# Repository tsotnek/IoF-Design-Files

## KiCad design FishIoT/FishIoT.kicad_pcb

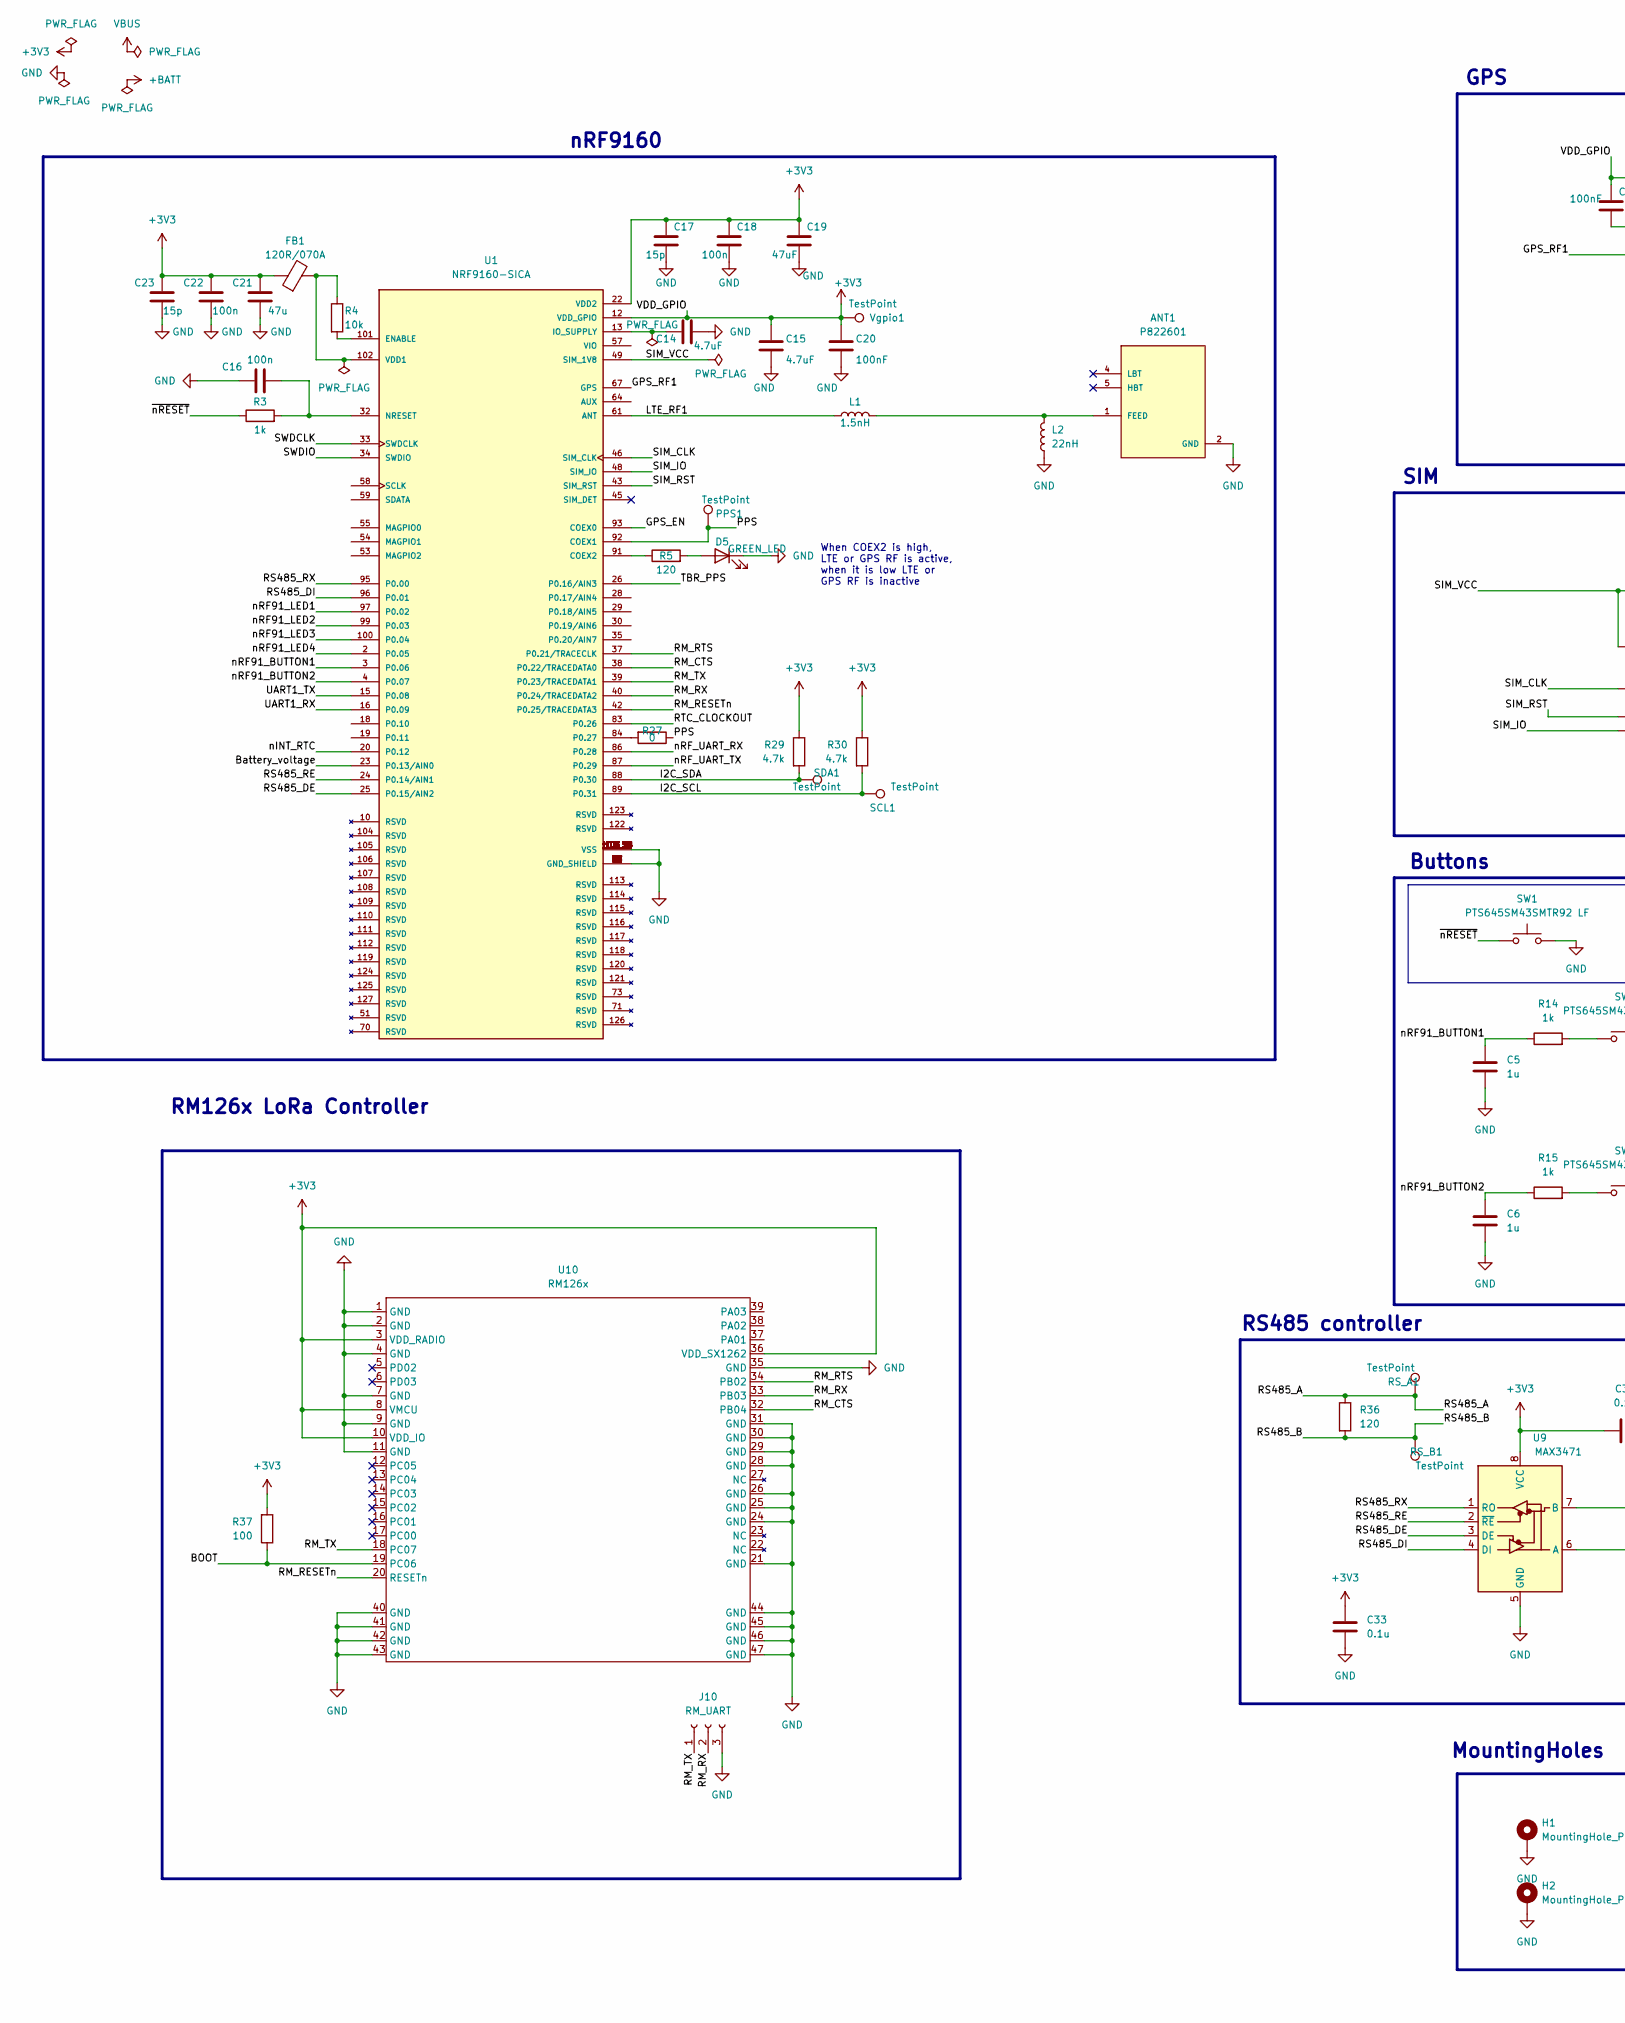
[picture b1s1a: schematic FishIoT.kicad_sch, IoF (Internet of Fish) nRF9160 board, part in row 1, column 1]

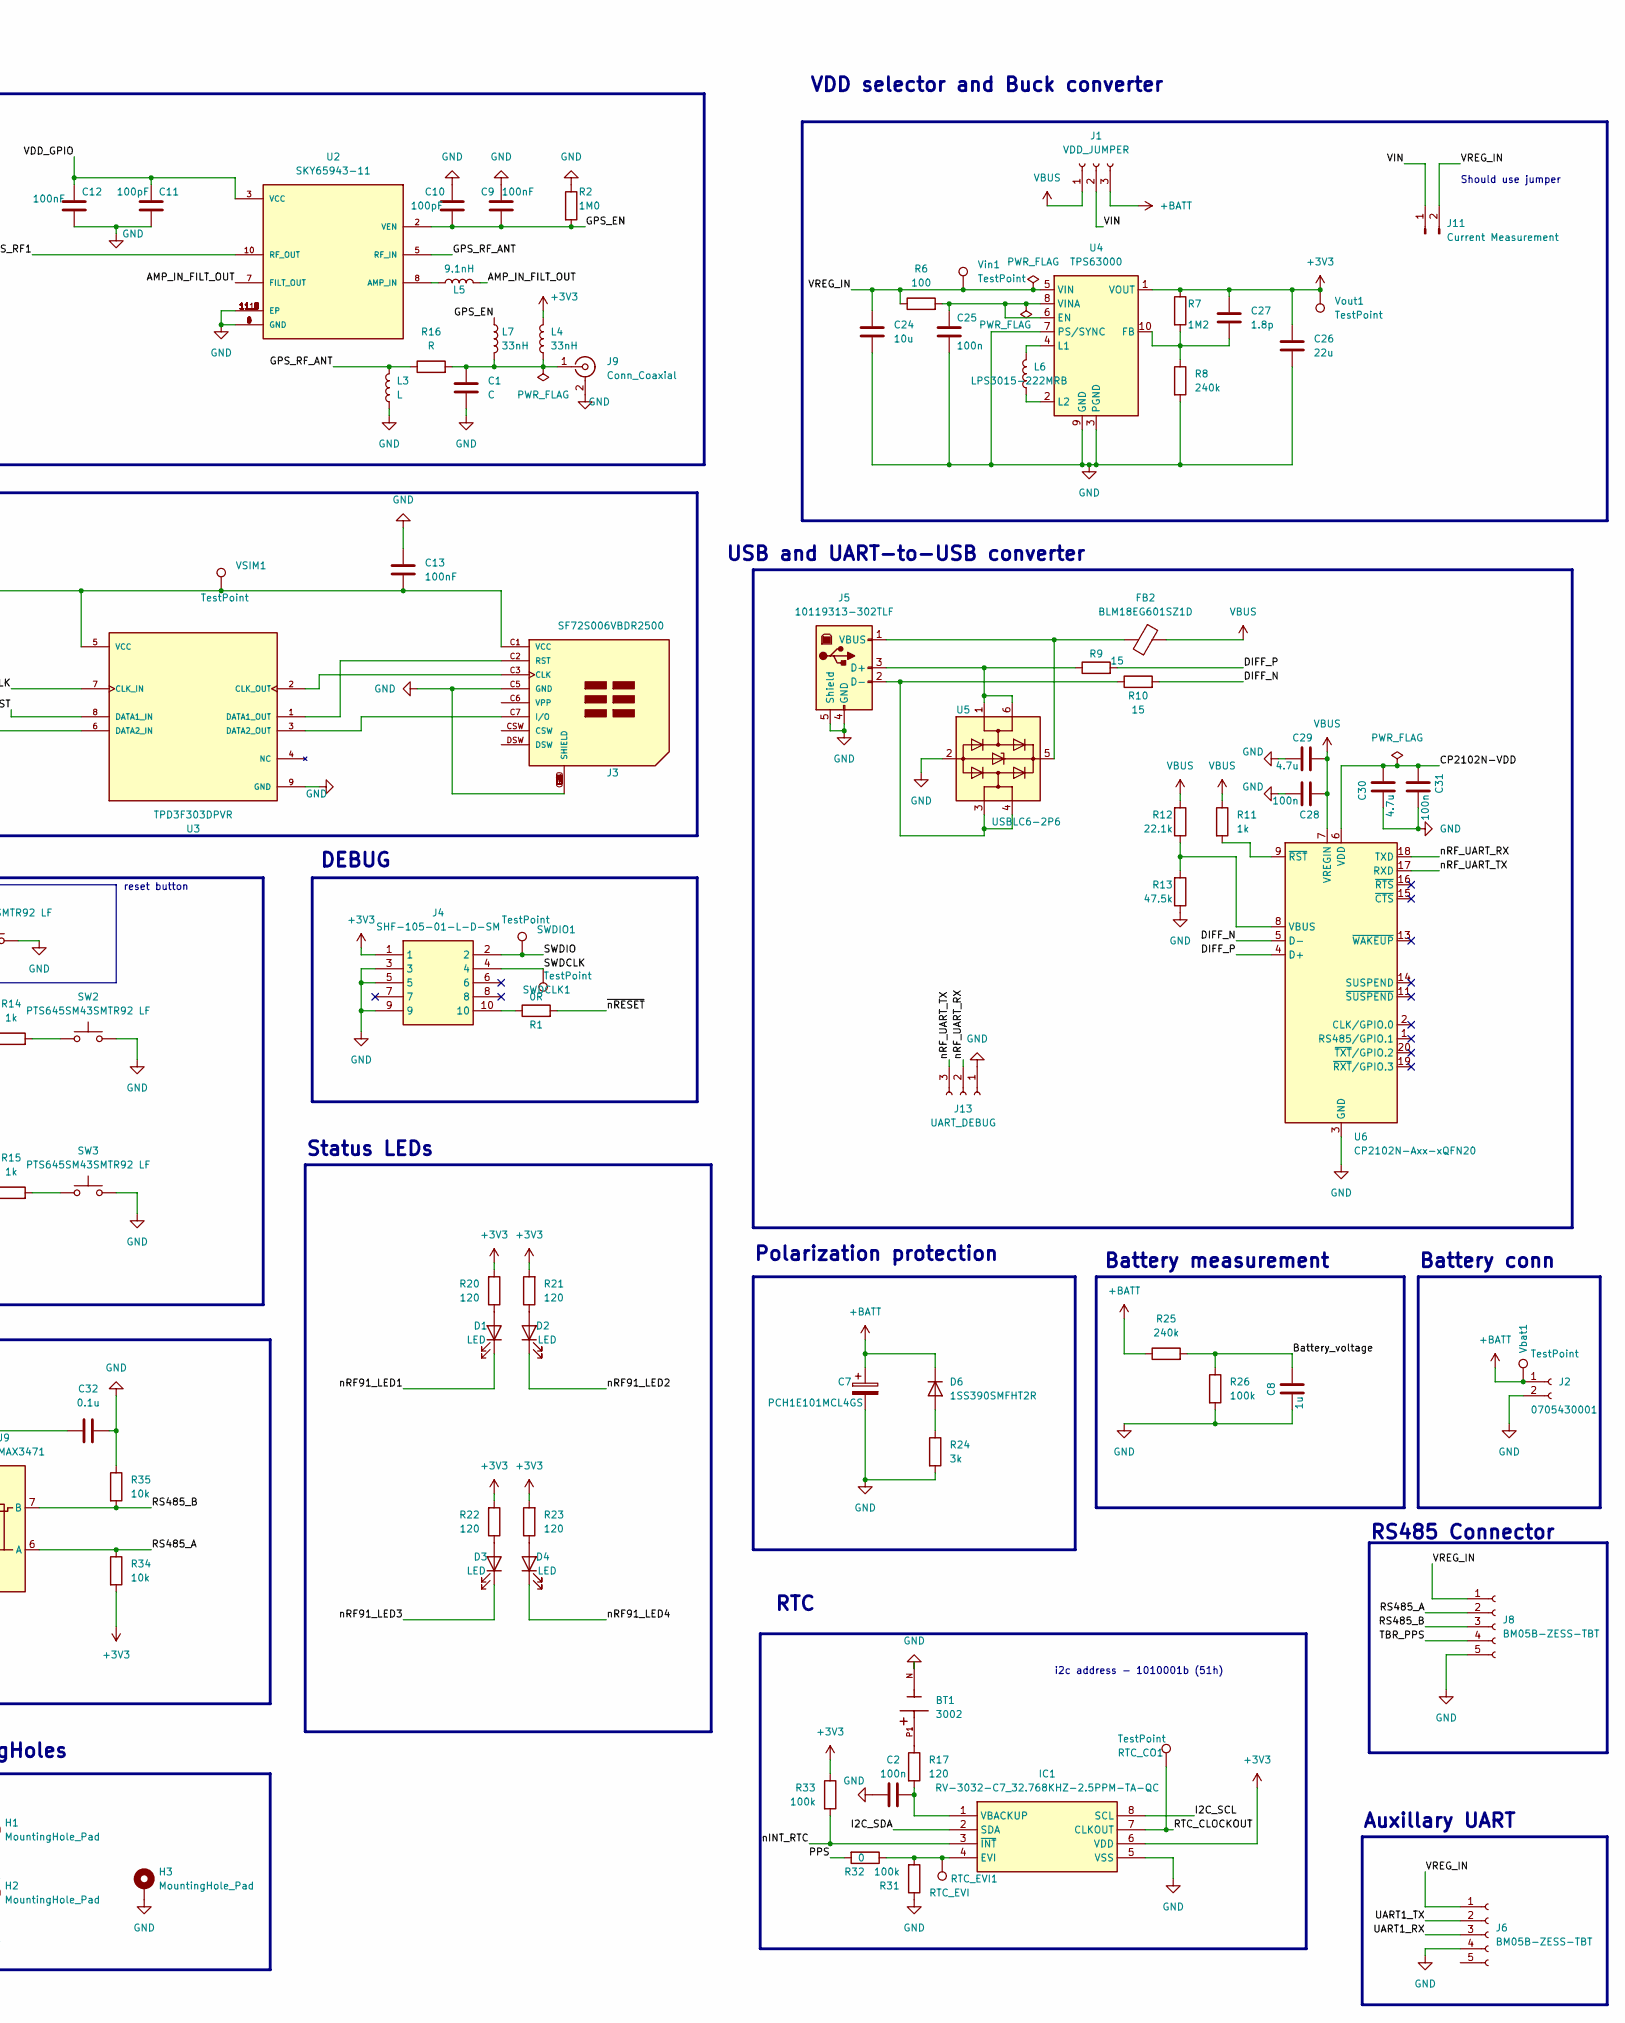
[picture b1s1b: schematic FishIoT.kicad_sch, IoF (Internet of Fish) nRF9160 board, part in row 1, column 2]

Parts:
ANT1: P822601; ANT_P822601
BT1: 3002; BAT_3002; PARTREV A
C1: C; C_0603_1608Metric
C2, C16, C18, C22, C25, C28, C31: 100n; C_0603_1608Metric
C5, C6, C8: 1u; C_0603_1608Metric
C7: PCH1E101MCL4GS; CP_Elec_6.3x7.7
C9, C12, C13, C20: 100nF; C_0603_1608Metric
C10, C11: 100pF; C_0603_1608Metric
C14, C15: 4.7uF; C_0603_1608Metric
C17, C23: 15p; C_0603_1608Metric
C19: 47uF; C_0603_1608Metric
C21: 47u; C_0603_1608Metric
C24: 10u; C_0603_1608Metric
C26: 22u; C_0603_1608Metric
C27: 1.8p; C_0603_1608Metric
C29, C30: 4.7u; C_0603_1608Metric
C32, C33: 0.1u; C_0603_1608Metric
D1, D2, D3, D4: LED; LED_0603_1608Metric
D5: GREEN_LED; LED_0603_1608Metric
D6: 1SS390SMFHT2R; D_SOD-523
FB1: 120R/070A; L_0603_1608Metric
FB2: BLM18EG601SZ1D; L_0603_1608Metric
H1, H2, H3: MountingHole_Pad; MountingHole_3mm_Pad_Via
IC1: RV-3032-C7_32.768KHZ-2.5PPM-TA-QC; RV3032C7; Mouser Part Number 428-203803-MG01
J1: VDD_JUMPER; PinHeader_1x03_P2.54mm_Vertical
J2: 0705430001; MOLEX_0705430001
J3: SF72S006VBDR2500; JAE_SF72S006VBDR2500
J4: SHF-105-01-L-D-SM; SHF-105-01-X-D-SM; Mouser Part Number 200-SHF10501LDSM
J5: 10119313-302TLF; AMPHENOL_10119313-302TLF
J6, J8: BM05B-ZESS-TBT; BM05BZESSTBTLFSN
J9: Conn_Coaxial; LINX_CONUFL001-SMD-T
J10: RM_UART; PinHeader_1x03_P2.54mm_Vertical
J11: Current Measurement; PinHeader_1x02_P2.54mm_Vertical
J13: UART_DEBUG; PinHeader_1x03_P2.54mm_Vertical
L1: 1.5nH; L_0603_1608Metric
L2: 22nH; L_0603_1608Metric
L3: L; L_0603_1608Metric
L4, L7: 33nH; L_0603_1608Metric
L5: 9.1nH; L_0603_1608Metric
L6: LPS3015-222MRB; L_Vishay_IHLP-1212
PPS1: TestPoint; TestPoint_Pad_D1.0mm
R1: 0R; R_0603_1608Metric
R2: 1M0; R_0603_1608Metric
R3, R11, R14, R15: 1k; R_0603_1608Metric
R4, R34, R35: 10k; R_0603_1608Metric
R5, R17, R20, R21, R22, R23, R36: 120; R_0603_1608Metric
R6, R37: 100; R_0603_1608Metric
R7: 1M2; R_0603_1608Metric
R8, R25: 240k; R_0603_1608Metric
R9, R10: 15; R_0603_1608Metric
R12: 22.1k; R_0603_1608Metric
R13: 47.5k; R_0603_1608Metric
R16: R; R_0603_1608Metric
R24: 3k; R_0603_1608Metric
R26, R31, R33: 100k; R_0603_1608Metric
R27, R32: 0; R_0603_1608Metric
R29, R30: 4.7k; R_0603_1608Metric
RS_A1: TestPoint; TestPoint_Pad_D1.0mm
RS_B1: TestPoint; TestPoint_Pad_D1.0mm
RTC_CO1: TestPoint; TestPoint_Pad_D1.0mm
RTC_EVI1: RTC_EVI; TestPoint_Pad_D1.0mm
SCL1: TestPoint; TestPoint_Pad_D1.0mm
SDA1: TestPoint; TestPoint_Pad_D1.0mm
SW1, SW2, SW3: PTS645SM43SMTR92 LF; SW_Push_1P1T_NO_6x6mm_H9.5mm
SWDCLK1: TestPoint; TestPoint_Pad_D1.0mm
SWDIO1: TestPoint; TestPoint_Pad_D1.0mm
U1: NRF9160-SICA; XCVR_NRF9160-SICA; PARTREV 0.7.1
U2: SKY65943-11; IC_SKY65943-11; PARTREV September 12, 2019
U3: TPD3F303DPVR; SON50P210X160X65-9N
U4: TPS63000; Texas_DRC0010J_ThermalVias
U5: USBLC6-2P6; SOT-666
U6: CP2102N-Axx-xQFN20; SiliconLabs_QFN-20-1EP_3x3mm_P0.5mm_EP1.8x1.8mm
U9: MAX3471; TSSOP-8_3x3mm_P0.65mm
U10: RM126x; Laird, RM126X
VSIM1: TestPoint; TestPoint_Pad_D1.0mm
Vbat1: TestPoint; TestPoint_Pad_D1.0mm
Vgpio1: TestPoint; TestPoint_Pad_D1.0mm
Vin1: TestPoint; TestPoint_Pad_D1.0mm
Vout1: TestPoint; TestPoint_Pad_D1.0mm

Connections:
+3V3: C11.2, C12.1, C15.1, C17.1, C18.1, C19.1, C20.1, C21.2, C22.2, C23.2, C26.1, C27.1, C32.2, C33.1, FB1.1, IC1.6 (VDD), J4.1, L4.2, R7.1, R20.2, R21.2, R22.2, R23.2, R29.1, R30.1, R33.1, R34.2, R37.2, U1.12 (VDD_GPIO), U1.22 (VDD2), U2.3 (VCC), U4.1 (VOUT), U9.8 (VCC), U10.3 (VDD_RADIO), U10.8 (VMCU), U10.10 (VDD_IO), U10.36 (VDD_SX1262), Vgpio1.1, Vout1.1
+BATT: C7.1, D6.1 (K), J1.3, J2.1, R25.1, Vbat1.1
/AMP_IN_FILT_OUT: L5.2, U2.7 (FILT_OUT)
/BOOT: R37.1, U10.19 (PC06)
/Battery_voltage: C8.2, R25.2, R26.1, U1.23 (P0.13/AIN0)
/CP2102N-VDD: C30.2, C31.2, U6.6 (VDD)
/DIFF_N: R10.2, U6.5 (D-)
/DIFF_P: R9.2, U6.4 (D+)
/GPS_EN: C9.1, C10.2, L7.1, R2.2, U1.93 (COEX0), U2.2 (VEN)
/GPS_RF1: U1.67 (GPS), U2.10 (RF_OUT)
/GPS_RF_ANT: L3.2, R16.1, U2.5 (RF_IN)
/I2C_SCL: IC1.8 (SCL), R30.2, SCL1.1, U1.89 (P0.31)
/I2C_SDA: IC1.2 (SDA), R29.2, SDA1.1, U1.88 (P0.30)
/LTE_RF1: L1.1, U1.61 (ANT)
/PPS: PPS1.1, R27.1, R32.2, U1.92 (COEX1)
/RM_CTS: U1.38 (P0.22/TRACEDATA0), U10.32 (PB04)
/RM_RESETn: U1.42 (P0.25/TRACEDATA3), U10.20 (RESETn)
/RM_RTS: U1.37 (P0.21/TRACECLK), U10.34 (PB02)
/RM_RX: J10.2, U1.40 (P0.24/TRACEDATA2), U10.33 (PB03)
/RM_TX: J10.1, U1.39 (P0.23/TRACEDATA1), U10.18 (PC07)
/RS485_A: J8.2, R34.1, R36.1, RS_A1.1, U9.6 (A)
/RS485_B: J8.3, R35.2, R36.2, RS_B1.1, U9.7 (B)
/RS485_DE: U1.25 (P0.15/AIN2), U9.3 (DE)
/RS485_DI: U1.96 (P0.01), U9.4 (DI)
/RS485_RE: U1.24 (P0.14/AIN1), U9.2 (~RE)
/RS485_RX: U1.95 (P0.00), U9.1 (RO)
/RTC_CLOCKOUT: IC1.7 (CLKOUT), RTC_CO1.1, U1.83 (P0.26)
/SIM_CLK: U1.46 (SIM_CLK), U3.7 (CLK_IN)
/SIM_IO: U1.48 (SIM_IO), U3.6 (DATA2_IN)
/SIM_RST: U1.43 (SIM_RST), U3.8 (DATA1_IN)
/SIM_VCC: C13.2, J3.C1 (VCC), U1.49 (SIM_1V8), U3.5 (VCC), VSIM1.1
/SWDCLK: J4.4, SWDCLK1.1, U1.33 (SWDCLK)
/SWDIO: J4.2, SWDIO1.1, U1.34 (SWDIO)
/TBR_PPS: J8.4, U1.26 (P0.16/AIN3)
/UART1_RX: J6.3, U1.16 (P0.09)
/UART1_TX: J6.2, U1.15 (P0.08)
/VIN: J1.2, J11.1
/VREG_IN: C24.1, J6.1, J8.1, J11.2, R6.1, U4.5 (VIN), Vin1.1
/nINT_RTC: IC1.3 (~INT), R33.2, U1.20 (P0.12)
/nRF91_BUTTON1: C5.1, R14.1, U1.3 (P0.06)
/nRF91_BUTTON2: C6.1, R15.1, U1.4 (P0.07)
/nRF91_LED1: D1.1 (K), U1.97 (P0.02)
/nRF91_LED2: D2.1 (K), U1.99 (P0.03)
/nRF91_LED3: D3.1 (K), U1.100 (P0.04)
/nRF91_LED4: D4.1 (K), U1.2 (P0.05)
/nRF_UART_RX: J13.2, U1.86 (P0.28), U6.18 (TXD)
/nRF_UART_TX: J13.3, U1.87 (P0.29), U6.17 (RXD)
/~nRESET: R1.2, R3.1, SW1.1
GND: ANT1.2 (GND), BT1.N, C1.2, C2.1, C5.2, C6.2, C7.2, C8.1, C9.2, C10.1, C11.1, C12.2, C13.1, C14.1, C15.2, C16.1, C17.2, C18.2, C19.2, C20.2, C21.1, C22.1, C23.1, C24.2, C25.2, C26.2, C28.1, C29.1, C30.1, C31.1, C32.1, C33.2, D5.1 (K), H1.1, H2.1, H3.1, IC1.5 (VSS), J2.2, J3.C5 (GND), J3.G1 (SHIELD), J3.G2 (SHIELD), J3.G3 (SHIELD), J3.G4 (SHIELD), J3.G5 (SHIELD), J3.G6 (SHIELD), J3.G7 (SHIELD), J3.G8 (SHIELD), J3.G9 (SHIELD), J3.G10 (SHIELD), J4.3, J4.5, J4.9, J5.4 (GND), J5.5 (Shield), J6.4, J8.5, J9.2 (Ext), J10.3, J13.1, L2.1, L3.1, R2.1, R8.2, R13.1, R24.2, R26.2, R31.1, R35.1, SW1.2, SW2.2, SW3.2, U1.1 (GND_SHIELD), U1.5 (GND_SHIELD), U1.6 (GND_SHIELD), U1.7 (GND_SHIELD), U1.8 (GND_SHIELD), U1.9 (GND_SHIELD), U1.11 (GND_SHIELD), U1.14 (GND_SHIELD), U1.17 (GND_SHIELD), U1.21 (GND_SHIELD), U1.27 (GND_SHIELD), U1.31 (GND_SHIELD), U1.36 (GND_SHIELD), U1.41 (GND_SHIELD), U1.44 (GND_SHIELD), U1.47 (GND_SHIELD), U1.50 (GND_SHIELD), U1.52 (GND_SHIELD), U1.56 (GND_SHIELD), U1.60 (GND_SHIELD), U1.62 (GND_SHIELD), U1.63 (GND_SHIELD), U1.65 (GND_SHIELD), U1.66 (GND_SHIELD), U1.68 (GND_SHIELD), U1.69 (GND_SHIELD), U1.72 (GND_SHIELD), U1.74 (GND_SHIELD), U1.75 (GND_SHIELD), U1.76 (GND_SHIELD), U1.77 (GND_SHIELD), U1.78 (GND_SHIELD), U1.79 (GND_SHIELD), U1.80 (GND_SHIELD), U1.81 (GND_SHIELD), U1.82 (GND_SHIELD), U1.85 (GND_SHIELD), U1.90 (GND_SHIELD), U1.94 (GND_SHIELD), U1.98 (GND_SHIELD), U1.103_1 (VSS), U1.103_2 (VSS), U1.103_3 (VSS), U1.103_4 (VSS), U1.103_5 (VSS), U1.103_6 (VSS), U1.103_7 (VSS), U1.103_8 (VSS), U1.103_9 (VSS), U1.103_10 (VSS), U1.103_11 (VSS), U1.103_12 (VSS), U1.103_13 (VSS), U1.103_14 (VSS), U1.103_15 (VSS), U1.103_16 (VSS), U1.103_17 (VSS), U1.103_18 (VSS), U1.103_19 (VSS), U1.103_20 (VSS), U1.103_21 (VSS), U1.103_22 (VSS), U1.103_23 (VSS), U1.103_24 (VSS), U1.103_25 (VSS), U1.103_26 (VSS), U1.103_27 (VSS), U1.103_28 (VSS), U1.103_29 (VSS), U1.103_30 (VSS), U1.103_31 (VSS), U1.103_32 (VSS), U1.103_33 (VSS), U1.103_34 (VSS), U1.103_35 (VSS), U2.1 (GND), U2.4 (GND), U2.6 (GND), U2.9 (GND), U2.11 (EP), U2.11_1 (EP), U2.11_2 (EP), U2.11_3 (EP), U2.11_4 (EP), U2.11_5 (EP), U2.11_6 (EP), U2.11_7 (EP), U2.11_8 (EP), U3.9 (GND), U4.3 (PGND), U4.7 (PS/SYNC), U4.9 (GND), U4.11 (PGND), U5.2 (GND), U6.3 (GND), U6.12 (GND), U6.21 (GND), U9.5 (GND), U10.1 (GND), U10.2 (GND), U10.4 (GND), U10.7 (GND), U10.9 (GND), U10.11 (GND), U10.21 (GND), U10.24 (GND), U10.25 (GND), U10.26 (GND), U10.28 (GND), U10.29 (GND), U10.30 (GND), U10.31 (GND), U10.35 (GND), U10.40 (GND), U10.41 (GND), U10.42 (GND), U10.43 (GND), U10.44 (GND), U10.45 (GND), U10.46 (GND), U10.47 (GND)
unnamed: ANT1.1 (FEED), L1.2, L2.2
unnamed: BT1.P1, R17.1
unnamed: D1.2 (A), R20.1
unnamed: D2.2 (A), R21.1
unnamed: D3.2 (A), R22.1
unnamed: D4.2 (A), R23.1
unnamed: D5.2 (A), R5.2
unnamed: D6.2 (A), R24.1
unnamed: IC1.4 (EVI), R31.2, R32.1, RTC_EVI1.1
unnamed: C2.2, IC1.1 (VBACKUP), R17.2
unnamed: J3.C3 (CLK), U3.2 (CLK_OUT)
unnamed: J3.C7 (I/O), U3.3 (DATA2_OUT)
unnamed: J3.C2 (RST), U3.1 (DATA1_OUT)
unnamed: J4.10, R1.1
unnamed: J5.3 (D+), R9.1, U5.1 (I/O1), U5.6 (I/O1)
unnamed: J5.2 (D-), R10.1, U5.3 (I/O2), U5.4 (I/O2)
unnamed: FB2.2, J5.1 (VBUS), U5.5 (VBUS)
unnamed: C1.1, J9.1 (In), L4.1, L7.2, R16.2
unnamed: R14.2, SW2.1
unnamed: R15.2, SW3.1
unnamed: R5.1, U1.91 (COEX2)
unnamed: R4.2, U1.101 (ENABLE)
unnamed: C14.2, U1.13 (IO_SUPPLY)
unnamed: C16.2, R3.2, U1.32 (NRESET)
unnamed: R27.2, U1.84 (P0.27)
unnamed: FB1.2, R4.1, U1.102 (VDD1)
unnamed: L5.1, U2.8 (AMP_IN)
unnamed: C25.1, R6.2, U4.6 (EN), U4.8 (VINA)
unnamed: C27.2, R7.2, R8.1, U4.10 (FB)
unnamed: L6.2, U4.4 (L1)
unnamed: L6.1, U4.2 (L2)
unnamed: R12.1, R13.2, U6.8 (VBUS)
unnamed: R11.2, U6.9 (~RST)
VBUS: C28.2, C29.2, FB2.1, J1.1, R11.1, R12.2, U6.7 (VREGIN)

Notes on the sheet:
MountingHoles
Polarization protection
When COEX2 is high, LTE or GPS RF is active, when it is low LTE or GPS RF is inactive
Battery conn
Status LEDs
Auxillary UART
RTC
nRF9160
i2c address - 1010001b (51h)
USB and UART-to-USB converter
Buttons
VDD selector and Buck converter
GPS
RS485 Connector
DEBUG
reset button
RS485 controller
SIM
Should use jumper
RM126x LoRa Controller
Battery measurement

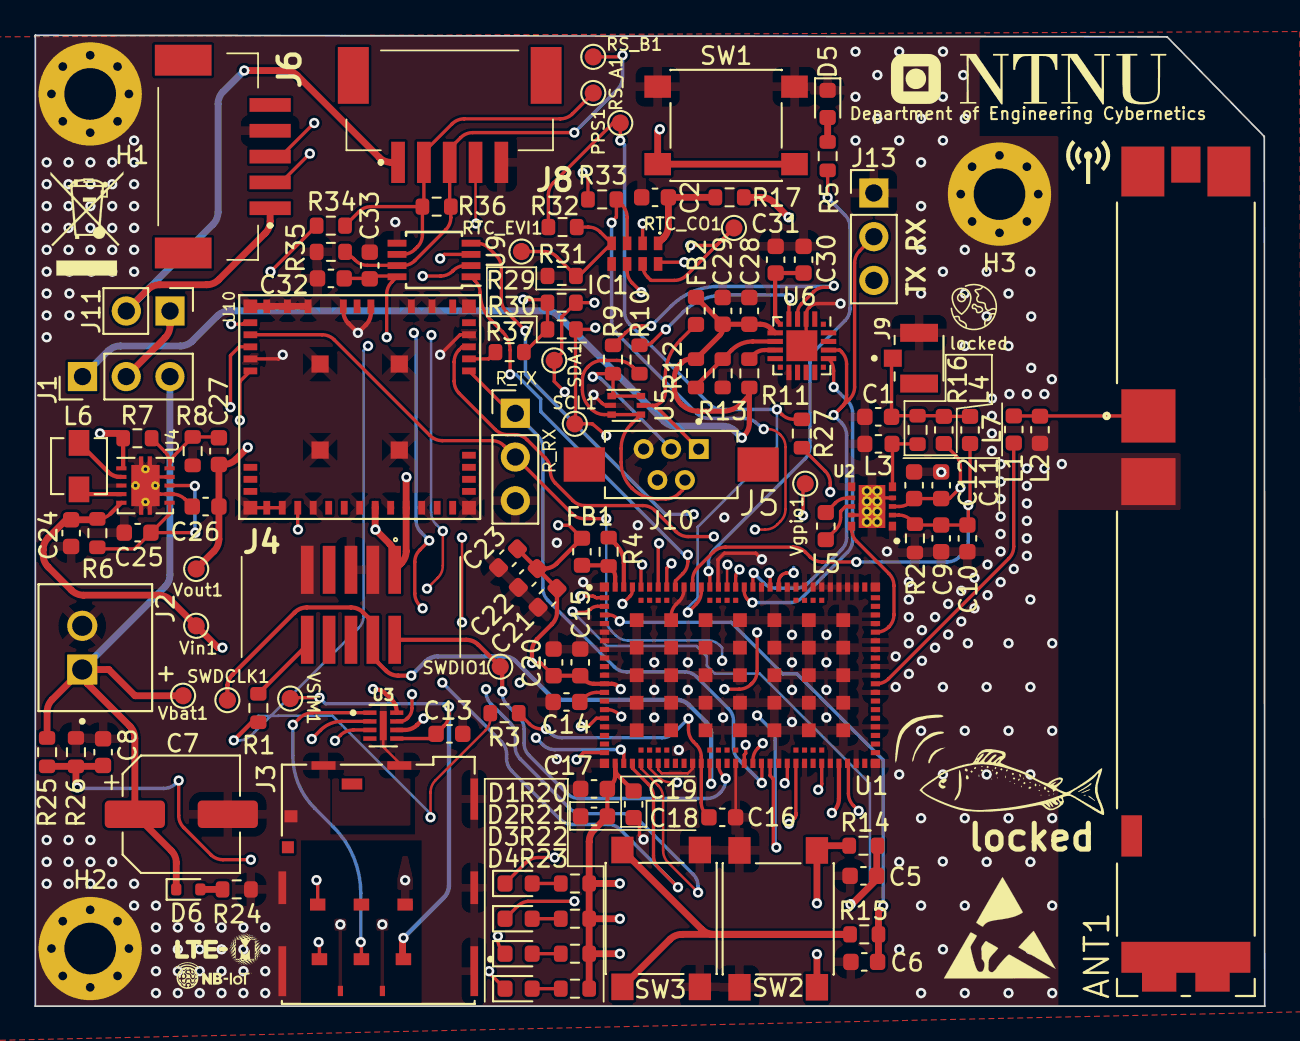
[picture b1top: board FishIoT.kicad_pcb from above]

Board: 4 copper layers, 71.4 x 56.4 mm, 122 parts (1 on the bottom side), 83 nets.

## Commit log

2023-11-24 schematic done
2023-11-24 added schematic image
2023-12-16 Changed GNSS antenna into u.fl. connector, decreased size of pcb further
2024-04-01 updated schematic and pcb
2024-04-03 removed MOS for leds, added RS connector
2024-04-19 Fixed a bug on batteryvoltage for ADC input pin
